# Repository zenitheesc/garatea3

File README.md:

<h1 align="center" style="color:white; background-color:black">Garatéa 3</h1>
<h4 align="center">Our aerospace probes are attached to balloons filled with helium, carrying astrobiological experiments to the stratosphere, which is crucial so we can have a better understanding about how organisms can survive in space.</h4>

<p align="center">

</p>

<p align="center">
    <a href="#what-are-aerospace-probes">What are aerospace probes?</a> •
    <a href="#project">Project</a> •
    <a href="#details">Details</a> 
</p>

## What are aerospace probes?

 Our aerospace probes are balloons filled with helium, carrying astrobiological experiments to the stratosphere, which is crucial so we can have a better understanding about how organisms can survive in space.

Although they are part of a greater scientific experiment, the probes themselves are also fascinating from the point of view of embedded systems development. Our probes are equiped with microcontrolers, radios, sensors and cameras; every mission we aim to improve our systems so we can make the next mission even more efficient.

And, to sustain all our experiments and systems, we build reliable and reusable structures, that let us go to space multiple times. 

## Project

Garatéa 3 is our most awarded Space Probe, winning 3rd Place in Best Design in the **Global Space Balloon Challenge 2018**.	This Space Probe was also a highlight at **Campus Party**. 

We continue to use the Arduino Toolchain to develop software, but we grandly improve the hardware. Our mainboard was made with 2 Atmega microcontrollers (Master/Slave) communicating through I2C. The Master was connected to the most relevant acquisition sensors, such as GPS, pressure sensor, DHT, and barometer. The data read by the Master is sent to the Slave and the Slave receive sent them through LoRa and saved them in physical memory (EEPROM and SD card). The Slave also controlled the servomotor.

Our structure is based on a **hypercube**. The external connectors were built with white ABS filament and the supports were made with a PLA filament. The center cube is made with carbon fiber plates and the external cube with carbon fiber tubes connected by the 3D printed parts.
 
### Component List

- **Main Atmega:**
    - GPS (U-Blox NEO MAX-M8Q)
    - GPS (Adafruit Ultimate Breakout)
    - Barometer (BMP180)
    - DHT sensor
    - LM1117 Regulator 
    - 7805 Regulator
- **Slave Atmega:**
    - LoRa
    - Radiometrix
    - Servomotor
    - SD card
    - EEPROM

## Details
| Launch Date |Max Altitude|Experiments|Awards
|--|--|--|--|
| 22/04/2018 | 31,6 km |Experiments with yeasts, fungi and protozoa|3rd Place in Best Design (GSBC 2018)

| | | |
|:-------------------------:|:-------------------------:|:-------------------------:|
| |  ||
|  | | | |

---

<p align="center">

</p>
<p align = "center">
<a href="zenith.eesc@gmail.com">zenith.eesc@gmail.com</a>
</p>

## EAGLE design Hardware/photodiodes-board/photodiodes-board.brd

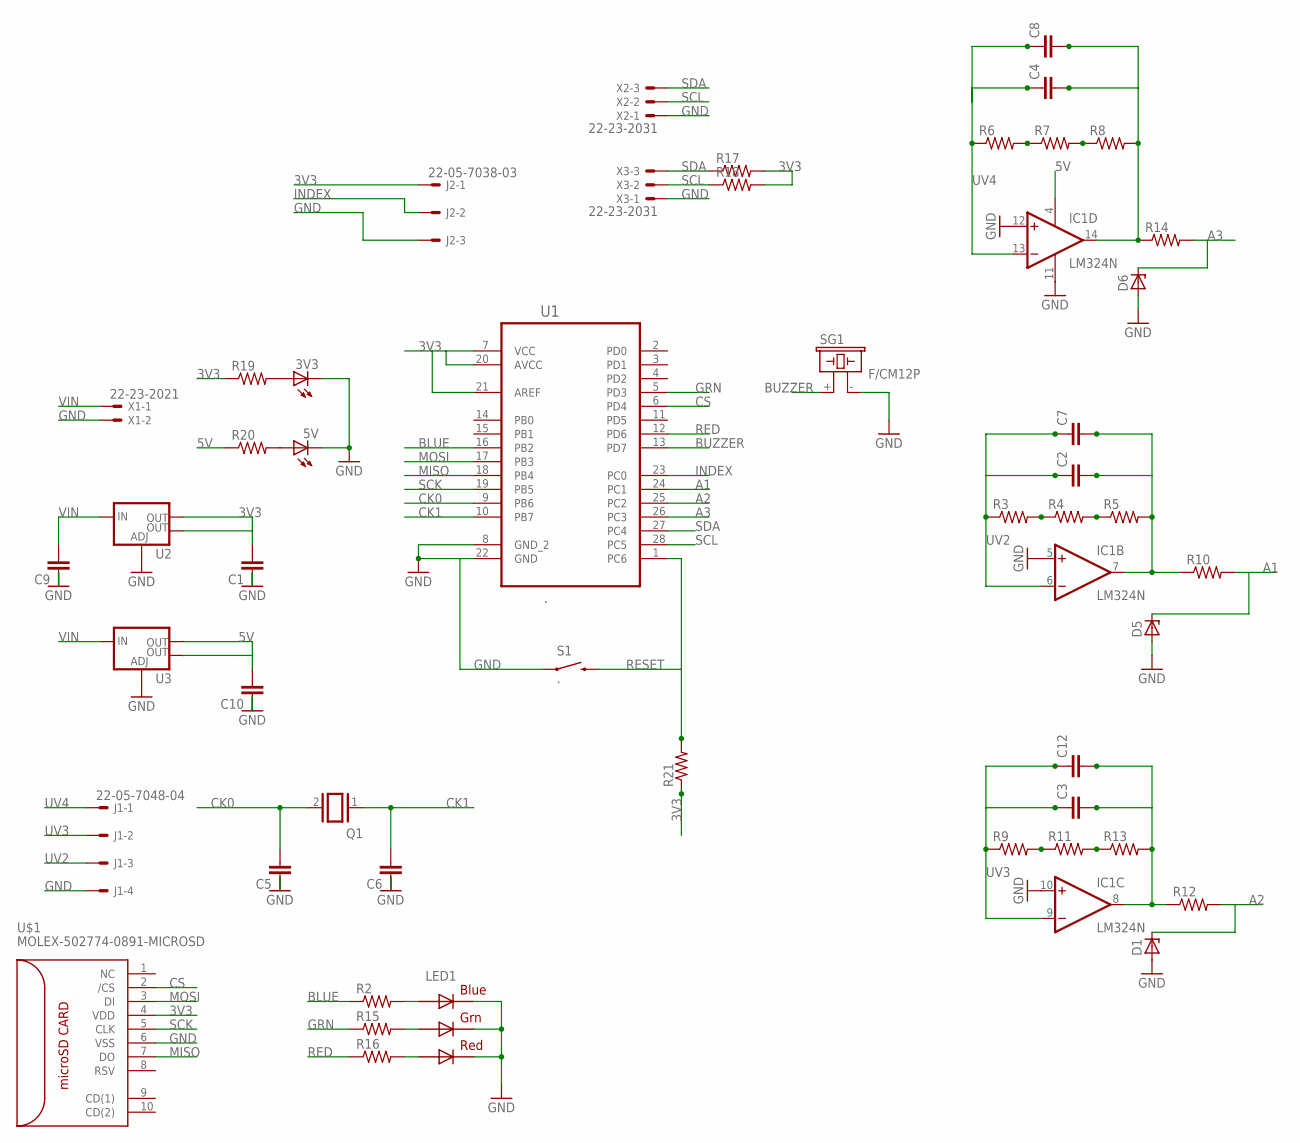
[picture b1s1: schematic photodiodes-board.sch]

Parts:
3V3, 5V: LEDSMT1206; 1206
C1, C2, C3, C4, C5, C6, C7, C8, C9, C10, C12: 10UF-1210-50V-20%; 1210
D1, D5, D6: ZENER-DIODEZD-12.5; ZDIO12.5
IC1: LM324N; DIL14
J1: 22-05-7048-04; 7395-04
J2: 22-05-7038-03; 7395-03
LED1: .; RGBLED5050
Q1: XTAL/S; QS
R2, R10, R12, R14, R15, R16, R17, R18, R19, R20, R21: R-US_M1206; M1206
R3, R4, R5, R6, R7, R8, R9, R11, R13: R-US_0207/12; 0207/12
S1: .; TACTILE-SWITCH-1101NE
SG1: F/CM12P
U1: .; DIP254P762X457-28
U2, U3: V_REG_LM1117SOT223; SOT223
U$1: MOLEX-502774-0891-MICROSD
X1: 22-23-2021
X2, X3: 22-23-2031

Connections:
3V3: C1.2, J2.1, R17.2, R18.2, R19.1, R21.1, U1.7 (VCC), U1.20 (AVCC), U1.21 (AREF), U2.2 (OUT), U2.4 (OUT), U$1.4 (VDD)
5V: C10.2, IC1.4 (V+), R20.1, U3.2 (OUT), U3.4 (OUT)
A1: D5.C, R10.2, U1.24 (PC1)
A2: D1.C, R12.2, U1.25 (PC2)
A3: D6.C, R14.2, U1.26 (PC3)
BLUE: R2.1, U1.16 (PB2)
BUZZER: SG1.+ (1), U1.13 (PD7)
CK0: C5.2, Q1.2, U1.9 (PB6)
CK1: C6.2, Q1.1, U1.10 (PB7)
CS: U1.6 (PD4), U$1.2 (/CS)
GND: 3V3.C, 5V.C, C1.1, C5.1, C6.1, C9.1, C10.1, D1.A, D5.A, D6.A, IC1.5 (+IN), IC1.10 (+IN), IC1.11 (V-), IC1.12 (+IN), J1.4, J2.3, LED1.4 (BLUE_C), LED1.5 (RED_C), LED1.6 (GREEN_C), S1.1, SG1.- (2), U1.8 (GND_2), U1.22 (GND), U2.1 (ADJ), U3.1 (ADJ), U$1.6 (VSS), X1.2, X2.1, X3.1
GRN: R15.1, U1.5 (PD3)
INDEX: J2.2, U1.23 (PC0)
MISO: U1.18 (PB4), U$1.7 (DO)
MOSI: U1.17 (PB3), U$1.3 (DI)
unnamed: R3.2, R4.1
unnamed: R4.2, R5.1
unnamed: R6.2, R7.1
unnamed: R7.2, R8.1
unnamed: R9.2, R11.1
unnamed: R11.2, R13.1
unnamed: LED1.3 (BLUE_A), R2.2
unnamed: LED1.1 (GREEN_A), R15.2
unnamed: LED1.2 (RED_A), R16.2
unnamed: 3V3.A, R19.2
unnamed: 5V.A, R20.2
unnamed: C4.2, C8.2, IC1.14 (OUT), R8.2, R14.1
unnamed: C3.2, C12.2, IC1.8 (OUT), R12.1, R13.2
unnamed: C2.2, C7.2, IC1.7 (OUT), R5.2, R10.1
RED: R16.1, U1.12 (PD6)
RESET: R21.2, S1.2, U1.1 (PC6)
SCK: U1.19 (PB5), U$1.5 (CLK)
SCL: R18.1, U1.28 (PC5), X2.2, X3.2
SDA: R17.1, U1.27 (PC4), X2.3, X3.3
UV2: C2.1, C7.1, IC1.6 (-IN), J1.3, R3.1
UV3: C3.1, C12.1, IC1.9 (-IN), J1.2, R9.1
UV4: C4.1, C8.1, IC1.13 (-IN), J1.1, R6.1
VIN: C9.2, U2.3 (IN), U3.3 (IN), X1.1

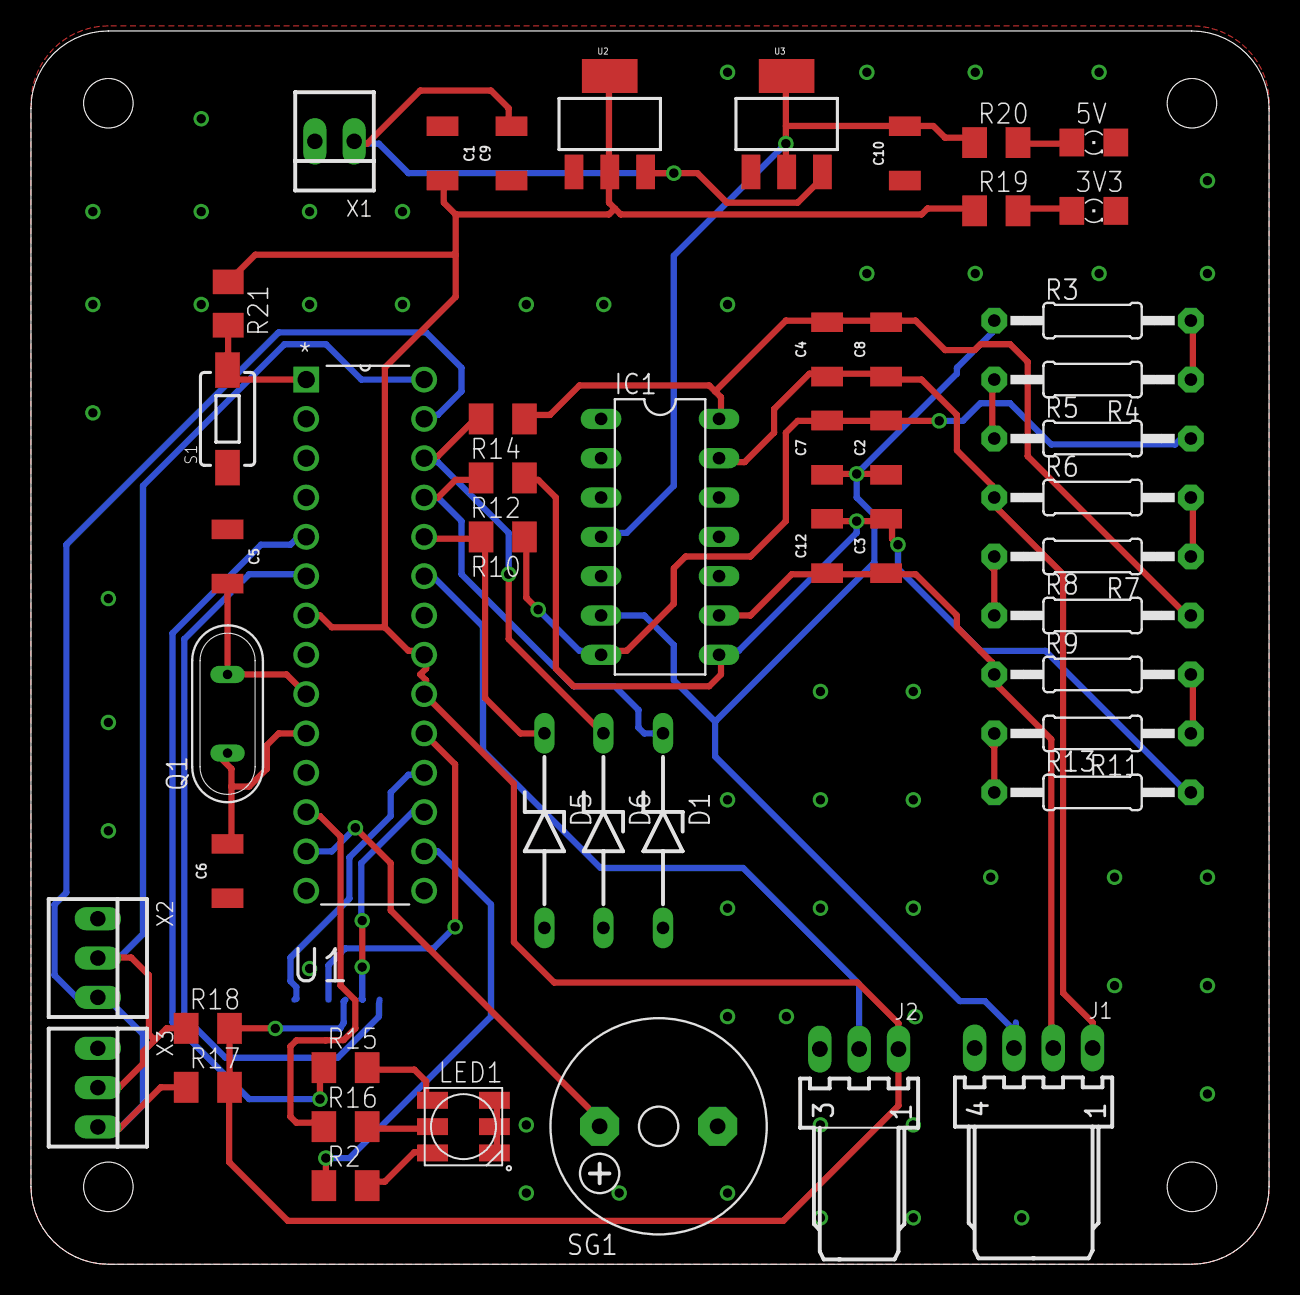
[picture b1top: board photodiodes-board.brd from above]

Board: 2 copper layers, 80.0 x 79.7 mm, 50 parts (1 on the bottom side), 38 nets.

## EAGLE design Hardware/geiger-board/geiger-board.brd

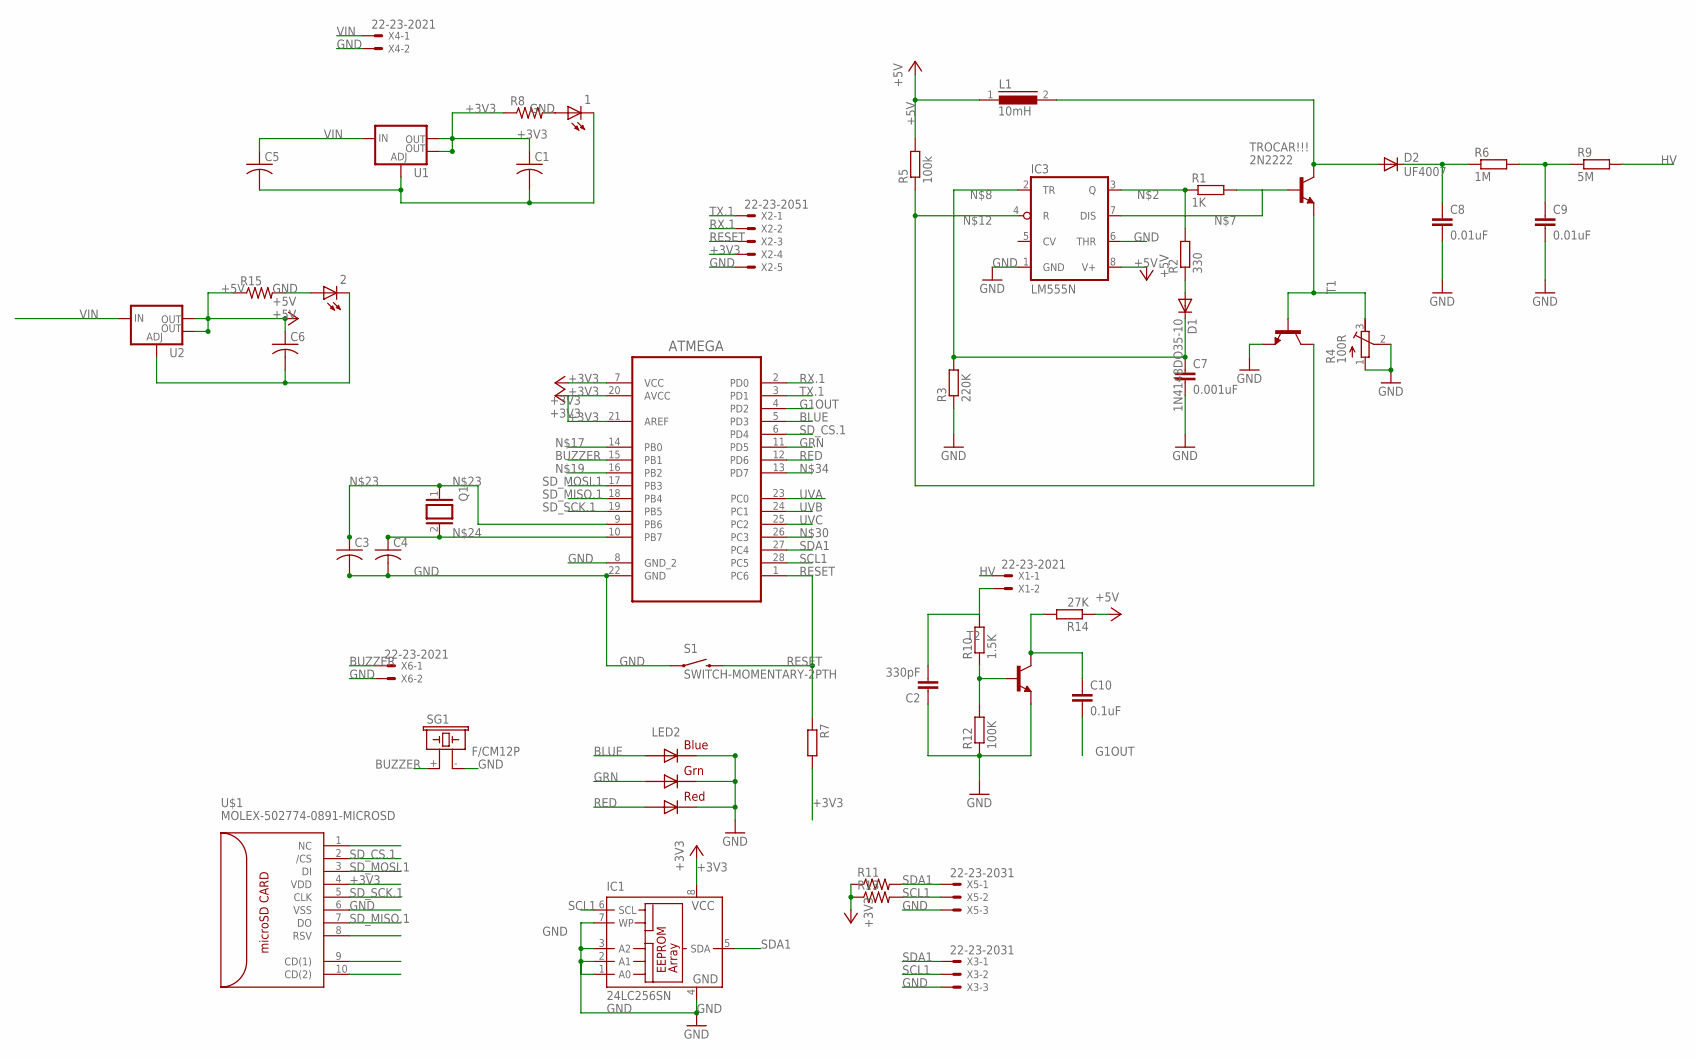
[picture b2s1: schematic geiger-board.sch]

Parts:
1, 2: LEDSMT1206; 1206
ATMEGA: ATMEGA328P-PU; DIP254P762X457-28
C1, C3, C4, C5, C6: C-USC1210K; C1210K
C2: 330pF; C5B4.5
C7: 0.001uF; C5B4.5
C8, C9: 0.01uF; C5B4.5
C10: 0.1uF; C5B4.5
D1: 1N4148DO35-10; DO35-10
D2: UF4007; DO35-10
IC1: 24LC256SN; SO-08
IC3: LM555N; DIL08-ROUND
L1: 10mH; 82114R
LED2: RGBLED5050
Q1: XTAL/S; QS
R1: 1K; 0207/10
R2: 330; 0207/10
R3: 220K; 0207/10
R4: 100R; RTRIM3296W
R5: 100k; 0207/10
R6: 1M; 0207/10
R7: R-EU_0207/10; 0207/10
R8, R15: R-US_M1206; M1206
R9: 5M; 0207/10
R10: 1.5K; 0207/10
R11, R13: R-US_R1206; R1206
R12: 100K; 0207/10
R14: 27K; 0207/10
S1: SWITCH-MOMENTARY-2PTH; TACTILE-PTH
SG1: F/CM12P
T1, T2: 2N4401-NPN-TO92-EBC; TO92-EBC
TROCAR!!!: 2N2222; TO92-EBC-OVAL
U1, U2: V_REG_LM1117SOT223; SOT223
U$1: MOLEX-502774-0891-MICROSD
X1, X4, X6: 22-23-2021
X2: 22-23-2051
X3, X5: 22-23-2031

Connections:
+3V3: ATMEGA.7 (VCC), ATMEGA.20 (AVCC), ATMEGA.21 (AREF), C1.1, IC1.8 (VCC), R7.2, R8.1, R11.1, R13.1, U1.2 (OUT), U1.4 (OUT), U$1.4 (VDD), X2.4
+5V: C6.1, IC3.8 (V+), L1.1, R5.2, R14.1, R15.1, U2.2 (OUT), U2.4 (OUT)
BLUE: ATMEGA.5 (PD3), LED2.3 (BLUE_A)
BUZZER: ATMEGA.15 (PB1), SG1.+ (1), X6.1
G1OUT: ATMEGA.4 (PD2), C10.2
GND: 1.C, 2.C, ATMEGA.8 (GND_2), ATMEGA.22 (GND), C1.2, C2.1, C3.2, C4.2, C5.2, C6.2, C7.2, C8.2, C9.2, IC1.1 (A0), IC1.2 (A1), IC1.3 (A2), IC1.4 (GND), IC1.7 (WP), IC3.1 (GND), IC3.6 (THR), LED2.4 (BLUE_C), LED2.5 (RED_C), LED2.6 (GREEN_C), R3.1, R4.1 (A), R4.2 (S), R12.1, S1.1, SG1.- (2), T1.E, T2.E, U1.1 (ADJ), U2.1 (ADJ), U$1.6 (VSS), X2.5, X3.3, X4.2, X5.3, X6.2
GRN: ATMEGA.11 (PD5), LED2.1 (GREEN_A)
HV: R9.2, X1.1
unnamed: 1.A, R8.2
unnamed: IC3.3 (Q), R1.1, R2.2
unnamed: 2.A, R15.2
unnamed: D1.A, R2.1
unnamed: IC3.7 (DIS), R1.2, TROCAR!!!.B
unnamed: C7.1, D1.C, IC3.2 (TR), R3.2
unnamed: D2.A, L1.2, TROCAR!!!.C
unnamed: C8.1, D2.C, R6.1
unnamed: IC3.4 (R), R5.1, T1.C
unnamed: C9.1, R6.2, R9.1
unnamed: C2.2, R10.2, X1.2
unnamed: R4.3 (E), T1.B, TROCAR!!!.E
unnamed: R10.1, R12.2, T2.B
unnamed: ATMEGA.9 (PB6), C3.1, Q1.1
unnamed: ATMEGA.10 (PB7), C4.1, Q1.2
unnamed: C10.1, R14.2, T2.C
RED: ATMEGA.12 (PD6), LED2.2 (RED_A)
RESET: ATMEGA.1 (PC6), R7.1, S1.3 (2), X2.3
RX.1: ATMEGA.2 (PD0), X2.2
SCL1: ATMEGA.28 (PC5), IC1.6 (SCL), R13.2, X3.2, X5.2
SDA1: ATMEGA.27 (PC4), IC1.5 (SDA), R11.2, X3.1, X5.1
SD_CS.1: ATMEGA.6 (PD4), U$1.2 (/CS)
SD_MISO.1: ATMEGA.18 (PB4), U$1.7 (DO)
SD_MOSI.1: ATMEGA.17 (PB3), U$1.3 (DI)
SD_SCK.1: ATMEGA.19 (PB5), U$1.5 (CLK)
TX.1: ATMEGA.3 (PD1), X2.1
UVA: ATMEGA.23 (PC0)
UVB: ATMEGA.24 (PC1)
UVC: ATMEGA.25 (PC2)
VIN: C5.1, U1.3 (IN), U2.3 (IN), X4.1

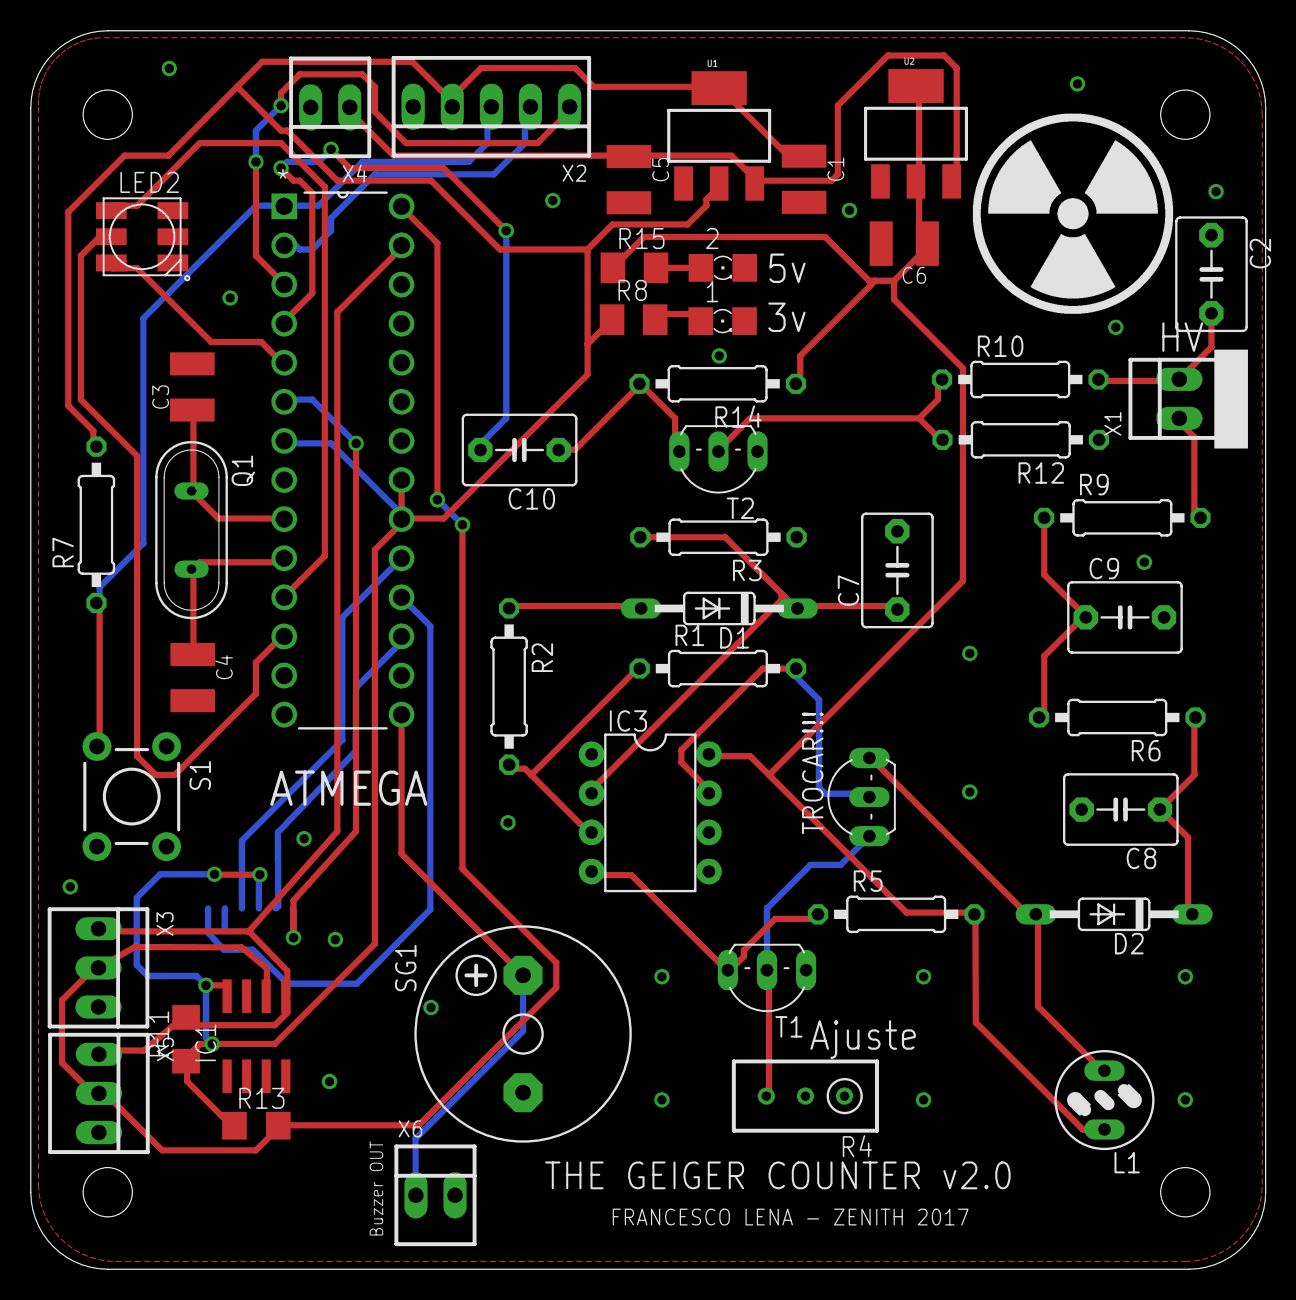
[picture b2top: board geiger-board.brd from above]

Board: 2 copper layers, 80.2 x 80.5 mm, 49 parts (1 on the bottom side), 35 nets.

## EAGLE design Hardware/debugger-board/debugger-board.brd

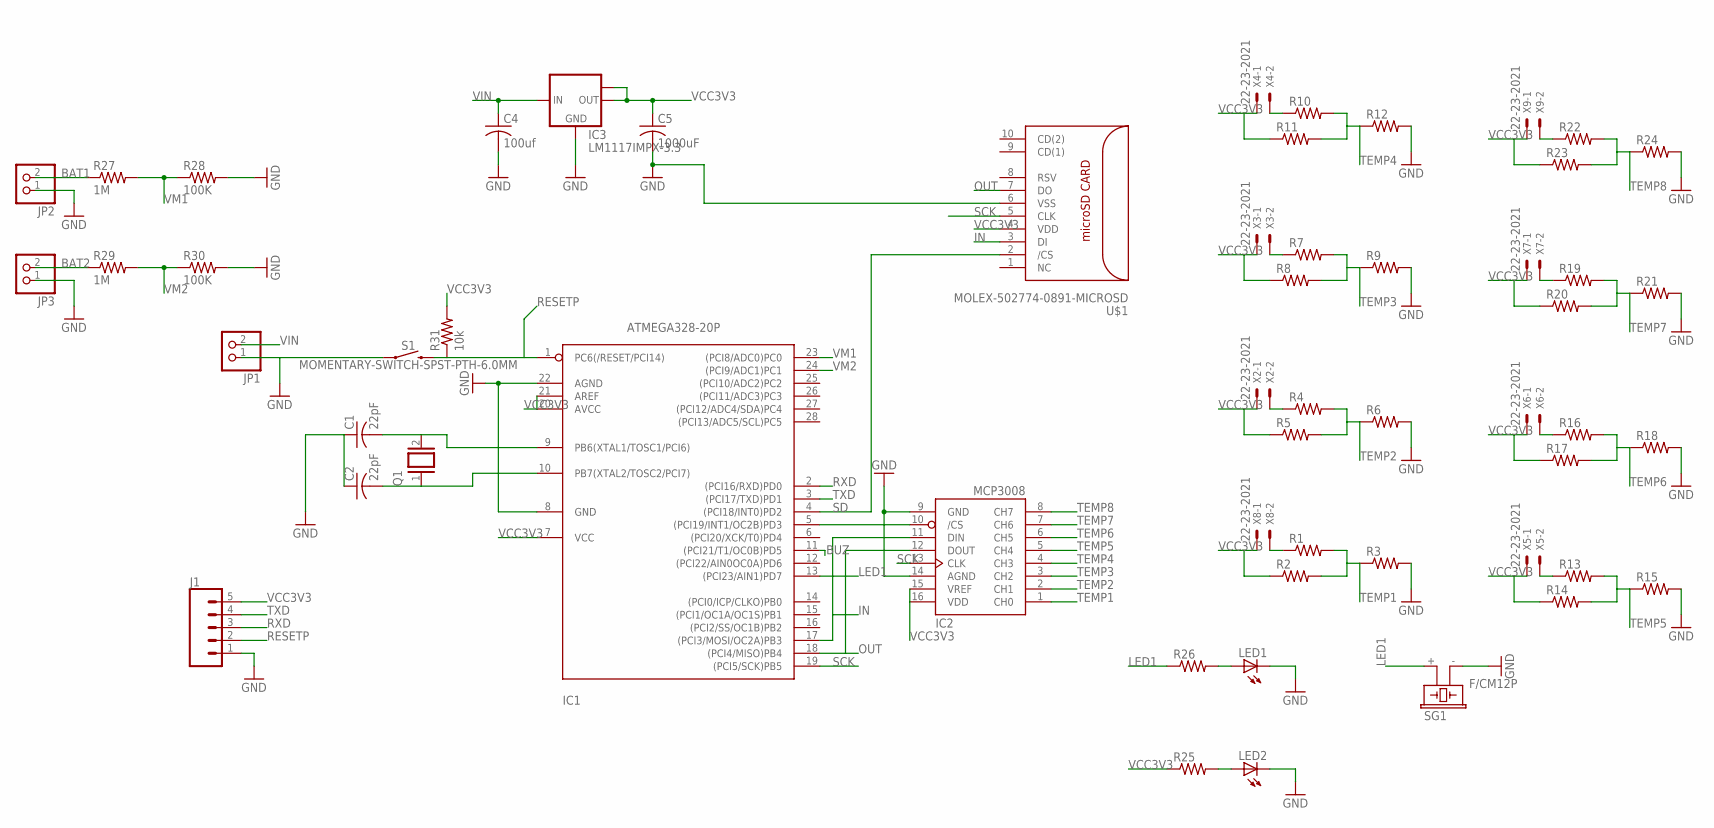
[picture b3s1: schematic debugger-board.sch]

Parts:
C1, C2: 22pF; C050-025X075
C4: 100uf; C050-025X075
C5: 1000uF; C050-025X075
IC1: ATMEGA328-20P; DIL28-3
IC2: MCP3008; DIL16
IC3: LM1117IMPX-3.3; SOT223
J1: CONN_05PTH_LONGPADS; 1X05_LONGPADS
JP1, JP2, JP3: PINHD-1X2; 1X02
LED1, LED2: LED_ELD260; LED_LD260
Q1: XTAL/S; QS
R1, R2, R3, R4, R5, R6, R7, R8, R9, R10, R11, R12, R13, R14, R15, R16, R17, R18, R19, R20, R21, R22, R23, R24, R25, R26: R-US_0204/5; 0204/5
R27, R29: 1M; 0204/5
R28, R30: 100K; 0204/5
R31: 10k; 0207/7
S1: MOMENTARY-SWITCH-SPST-PTH-6.0MM; TACTILE_SWITCH_PTH_6.0MM
SG1: F/CM12P
U$1: MOLEX-502774-0891-MICROSD
X2, X3, X4, X5, X6, X7, X8, X9: 22-23-2021

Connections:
BAT1: JP2.2, R27.1
BAT2: JP3.2, R29.1
BUZ: IC1.11 ((PCI21/T1/OC0B)PD5)
GND: C1.1, C2.1, C4.2, C5.2, IC1.8 (GND), IC1.22 (AGND), IC2.9 (GND), IC2.14 (AGND), IC3.1 (GND), J1.1, JP1.1, JP2.1, JP3.1, LED1.K (C), LED2.K (C), R3.2, R6.2, R9.2, R12.2, R15.2, R18.2, R21.2, R24.2, R28.2, R30.2, S1.1, SG1.- (2), U$1.6 (VSS)
IN: IC1.17 ((PCI3/MOSI/OC2A)PB3), IC2.11 (DIN), U$1.3 (DI)
LED1: IC1.13 ((PCI23/AIN1)PD7), R26.1, SG1.+ (1)
unnamed: LED2.A, R25.2
unnamed: IC1.5 ((PCI19/INT1/OC2B)PD3), IC2.10 (/CS)
unnamed: C1.2, IC1.9 (PB6(XTAL1/TOSC1/PCI6)), Q1.2
unnamed: C2.2, IC1.10 (PB7(XTAL2/TOSC2/PCI7)), Q1.1
unnamed: R4.1, X2.2
unnamed: R1.1, X8.2
unnamed: LED1.A, R26.2
unnamed: R7.1, X3.2
unnamed: R10.1, X4.2
unnamed: R13.1, X5.2
unnamed: R16.1, X6.2
unnamed: R19.1, X7.2
unnamed: R22.1, X9.2
OUT: IC1.18 ((PCI4/MISO)PB4), IC2.12 (DOUT), U$1.7 (DO)
RESETP: IC1.1 (PC6(/RESET/PCI14)), J1.2, R31.1, S1.3 (2)
RXD: IC1.2 ((PCI16/RXD)PD0), J1.3
SCK: IC1.19 ((PCI5/SCK)PB5), IC2.13 (CLK), U$1.5 (CLK)
SD: IC1.4 ((PCI18/INT0)PD2), U$1.2 (/CS)
TEMP1: IC2.1 (CH0), R1.2, R2.2, R3.1
TEMP2: IC2.2 (CH1), R4.2, R5.2, R6.1
TEMP3: IC2.3 (CH2), R7.2, R8.2, R9.1
TEMP4: IC2.4 (CH3), R10.2, R11.2, R12.1
TEMP5: IC2.5 (CH4), R13.2, R14.2, R15.1
TEMP6: IC2.6 (CH5), R16.2, R17.2, R18.1
TEMP7: IC2.7 (CH6), R19.2, R20.2, R21.1
TEMP8: IC2.8 (CH7), R22.2, R23.2, R24.1
TXD: IC1.3 ((PCI17/TXD)PD1), J1.4
VCC3V3: C5.1, IC1.7 (VCC), IC1.20 (AVCC), IC1.21 (AREF), IC2.15 (VREF), IC2.16 (VDD), IC3.2 (OUT), IC3.TAB (OUT1), J1.5, R2.1, R5.1, R8.1, R11.1, R14.1, R17.1, R20.1, R23.1, R25.1, R31.2, U$1.4 (VDD), X2.1, X3.1, X4.1, X5.1, X6.1, X7.1, X8.1, X9.1
VIN: C4.1, IC3.3 (IN), JP1.2
VM1: IC1.23 ((PCI8/ADC0)PC0), R27.2, R28.1
VM2: IC1.24 ((PCI9/ADC1)PC1), R29.2, R30.1

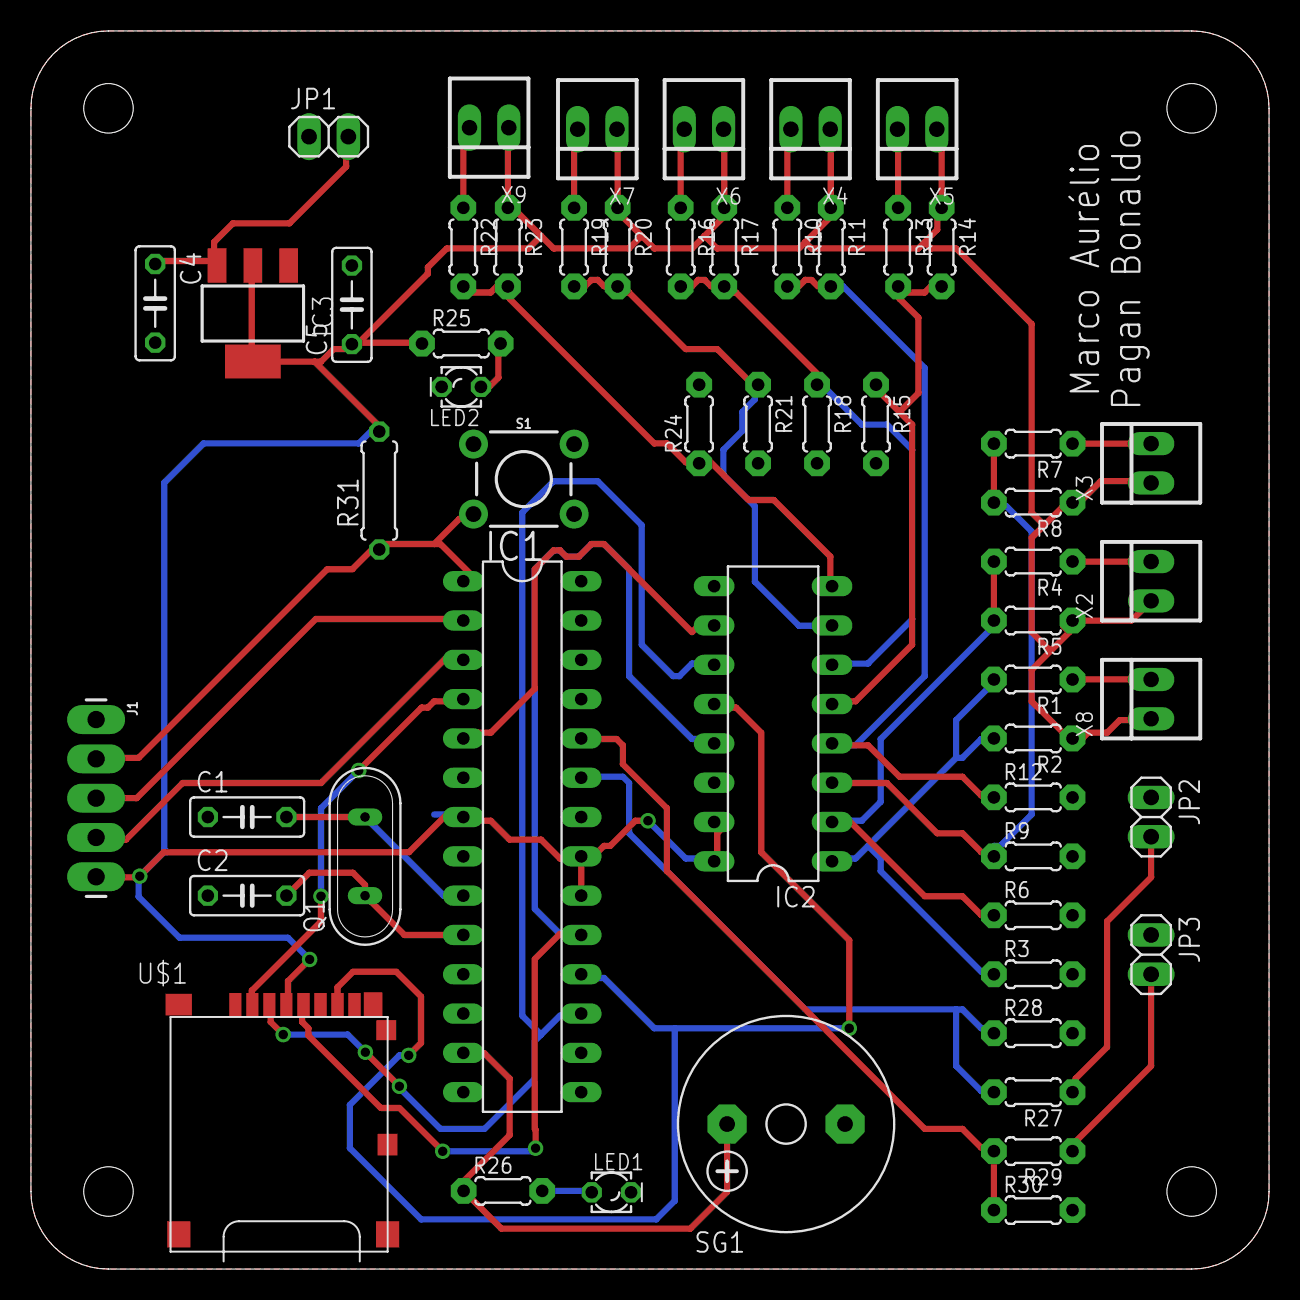
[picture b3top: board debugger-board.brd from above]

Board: 2 copper layers, 80.0 x 80.0 mm, 56 parts (0 on the bottom side), 36 nets.

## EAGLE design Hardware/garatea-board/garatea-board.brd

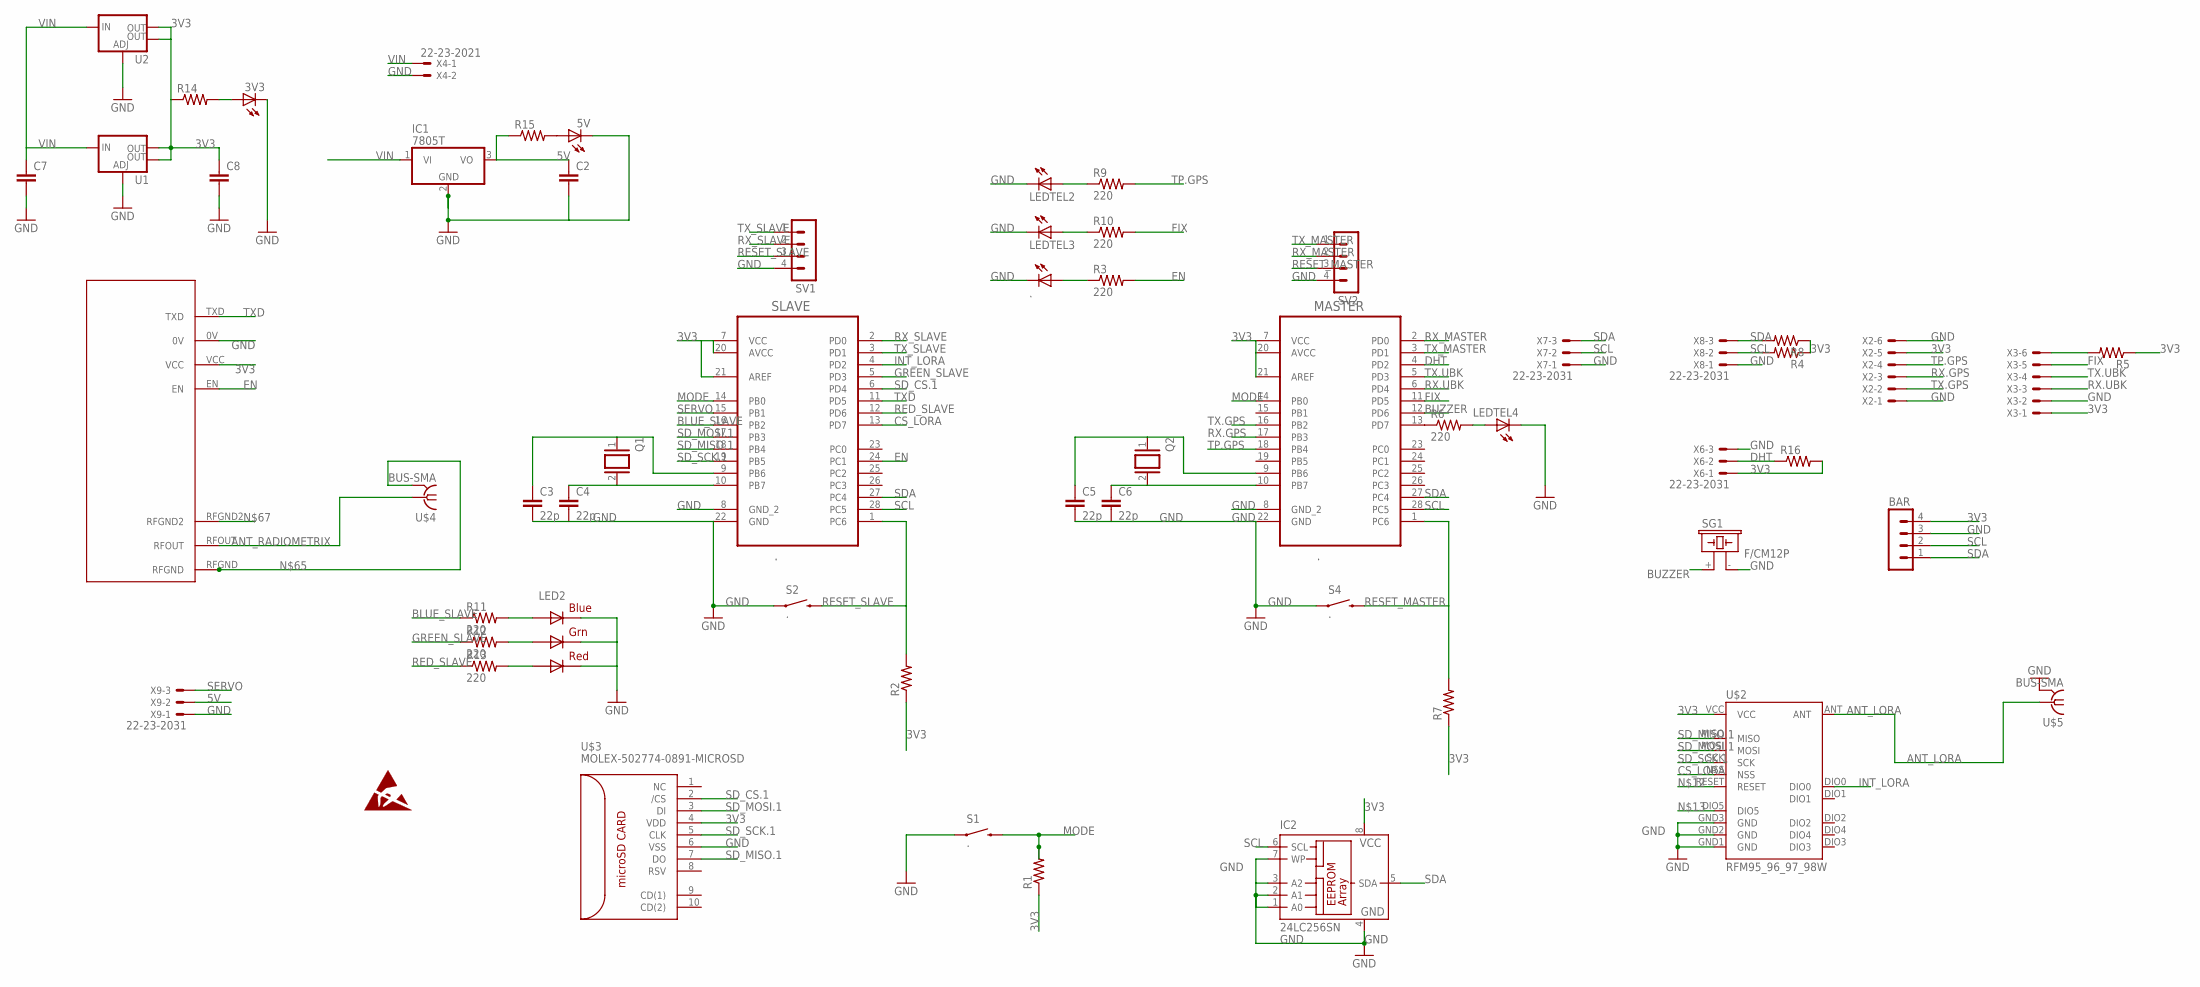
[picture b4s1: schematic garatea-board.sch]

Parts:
3V3, 5V, .: LEDSMT1206; 1206
BAR: MA04-1
C2, C7, C8: 10UF-1210-50V-20%; 1210
C3, C4, C5, C6: 22p; 1210
IC1: 7805T; TO220H
IC2: 24LC256SN; SO-08
LED2: RGBLED5050
LEDTEL2, LEDTEL3, LEDTEL4: LEDSMT1206; 1206
MASTER: .; DIP254P762X457-28
Q1, Q2: XTAL/S; QS
R1, R2, R4, R5, R7, R8, R14, R15, R16: R-US_M1206; M1206
R3, R6, R9, R10, R11, R12, R13: 220; M1206
S1, S2, S4: .; TACTILE-SWITCH-1101NE
SG1: F/CM12P
SLAVE: .; DIP254P762X457-28
SV1, SV2: MA04-1
U1, U2: V_REG_LM1117SOT223; SOT223
U$1: NTX2
U$2: RFM95_96_97_98W
U$3: MOLEX-502774-0891-MICROSD
U$4, U$5: BUS-SMA
X2, X3: 22-23-2061
X4: 22-23-2021
X6, X7, X8, X9: 22-23-2031

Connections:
3V3: BAR.4, C8.1, IC2.8 (VCC), MASTER.7 (VCC), MASTER.20 (AVCC), MASTER.21 (AREF), R1.1, R2.1, R4.1, R5.1, R7.1, R8.1, R14.1, R16.2, SLAVE.7 (VCC), SLAVE.20 (AVCC), SLAVE.21 (AREF), U1.2 (OUT), U1.4 (OUT), U2.2 (OUT), U2.4 (OUT), U$1.VCC, U$2.VCC, U$3.4 (VDD), X2.5, X3.1, X6.1
5V: C2.1, IC1.3 (VO), R15.1, X9.2
ANT_LORA: U$2.ANT, U$5.1
ANT_RADIOMETRIX: U$1.RFOUT, U$4.1
BLUE_SLAVE: R11.1, SLAVE.16 (PB2)
BUZZER: MASTER.12 (PD6), SG1.+ (1)
CS_LORA: SLAVE.13 (PD7), U$2.NSS
DHT: MASTER.4 (PD2), R16.1, X6.2
EN: R3.2, SLAVE.24 (PC1), U$1.EN
EN.UBK: R5.2, X3.6
FIX: MASTER.11 (PD5), R10.2, X3.5
GND: 3V3.C, 5V.C, ..C, BAR.3, C2.2, C3.2, C4.2, C5.2, C6.2, C7.2, C8.2, IC1.2 (GND), IC2.1 (A0), IC2.2 (A1), IC2.3 (A2), IC2.4 (GND), IC2.7 (WP), LED2.4 (BLUE_C), LED2.5 (RED_C), LED2.6 (GREEN_C), LEDTEL2.C, LEDTEL3.C, LEDTEL4.C, MASTER.8 (GND_2), MASTER.22 (GND), S1.1, S2.1, S4.1, SG1.- (2), SLAVE.8 (GND_2), SLAVE.22 (GND), SV1.4, SV2.4, U1.1 (ADJ), U2.1 (ADJ), U$1.0V, U$2.GND1 (GND), U$2.GND2 (GND), U$2.GND3 (GND), U$3.6 (VSS), U$5.2 (GND), U$5.3 (GND), U$5.4 (GND), U$5.5 (GND), X2.1, X2.6, X3.2, X4.2, X6.3, X7.1, X8.1, X9.1
GREEN_SLAVE: R12.1, SLAVE.5 (PD3)
INT_LORA: SLAVE.4 (PD2), U$2.DIO0
MODE: MASTER.14 (PB0), R1.2, S1.2, SLAVE.14 (PB0)
unnamed: MASTER.13 (PD7), R6.1
unnamed: LEDTEL3.A, R10.1
unnamed: LEDTEL2.A, R9.1
unnamed: ..A, R3.1
unnamed: 5V.A, R15.2
unnamed: LED2.3 (BLUE_A), R11.2
unnamed: LED2.1 (GREEN_A), R12.2
unnamed: LED2.2 (RED_A), R13.2
unnamed: 3V3.A, R14.2
unnamed: C6.1, MASTER.10 (PB7), Q2.2
unnamed: LEDTEL4.A, R6.2
unnamed: C3.1, Q1.1, SLAVE.9 (PB6)
unnamed: C4.1, Q1.2, SLAVE.10 (PB7)
unnamed: C5.1, MASTER.9 (PB6), Q2.1
unnamed: U$1.RFGND, U$4.2 (GND), U$4.3 (GND), U$4.4 (GND), U$4.5 (GND)
RED_SLAVE: R13.1, SLAVE.12 (PD6)
RESET_MASTER: MASTER.1 (PC6), R7.2, S4.2, SV2.3
RESET_SLAVE: R2.2, S2.2, SLAVE.1 (PC6), SV1.3
RX.GPS: MASTER.17 (PB3), X2.3
RX.UBK: MASTER.6 (PD4), X3.3
RX_MASTER: MASTER.2 (PD0), SV2.2
RX_SLAVE: SLAVE.2 (PD0), SV1.2
SCL: BAR.2, IC2.6 (SCL), MASTER.28 (PC5), R4.2, SLAVE.28 (PC5), X7.2, X8.2
SDA: BAR.1, IC2.5 (SDA), MASTER.27 (PC4), R8.2, SLAVE.27 (PC4), X7.3, X8.3
SD_CS.1: SLAVE.6 (PD4), U$3.2 (/CS)
SD_MISO.1: SLAVE.18 (PB4), U$2.MISO, U$3.7 (DO)
SD_MOSI.1: SLAVE.17 (PB3), U$2.MOSI, U$3.3 (DI)
SD_SCK.1: SLAVE.19 (PB5), U$2.SCK, U$3.5 (CLK)
SERVO: SLAVE.15 (PB1), X9.3
TP.GPS: MASTER.18 (PB4), R9.2, X2.4
TX.GPS: MASTER.16 (PB2), X2.2
TX.UBK: MASTER.5 (PD3), X3.4
TXD: SLAVE.11 (PD5), U$1.TXD
TX_MASTER: MASTER.3 (PD1), SV2.1
TX_SLAVE: SLAVE.3 (PD1), SV1.1
VIN: C7.1, IC1.1 (VI), U1.3 (IN), U2.3 (IN), X4.1

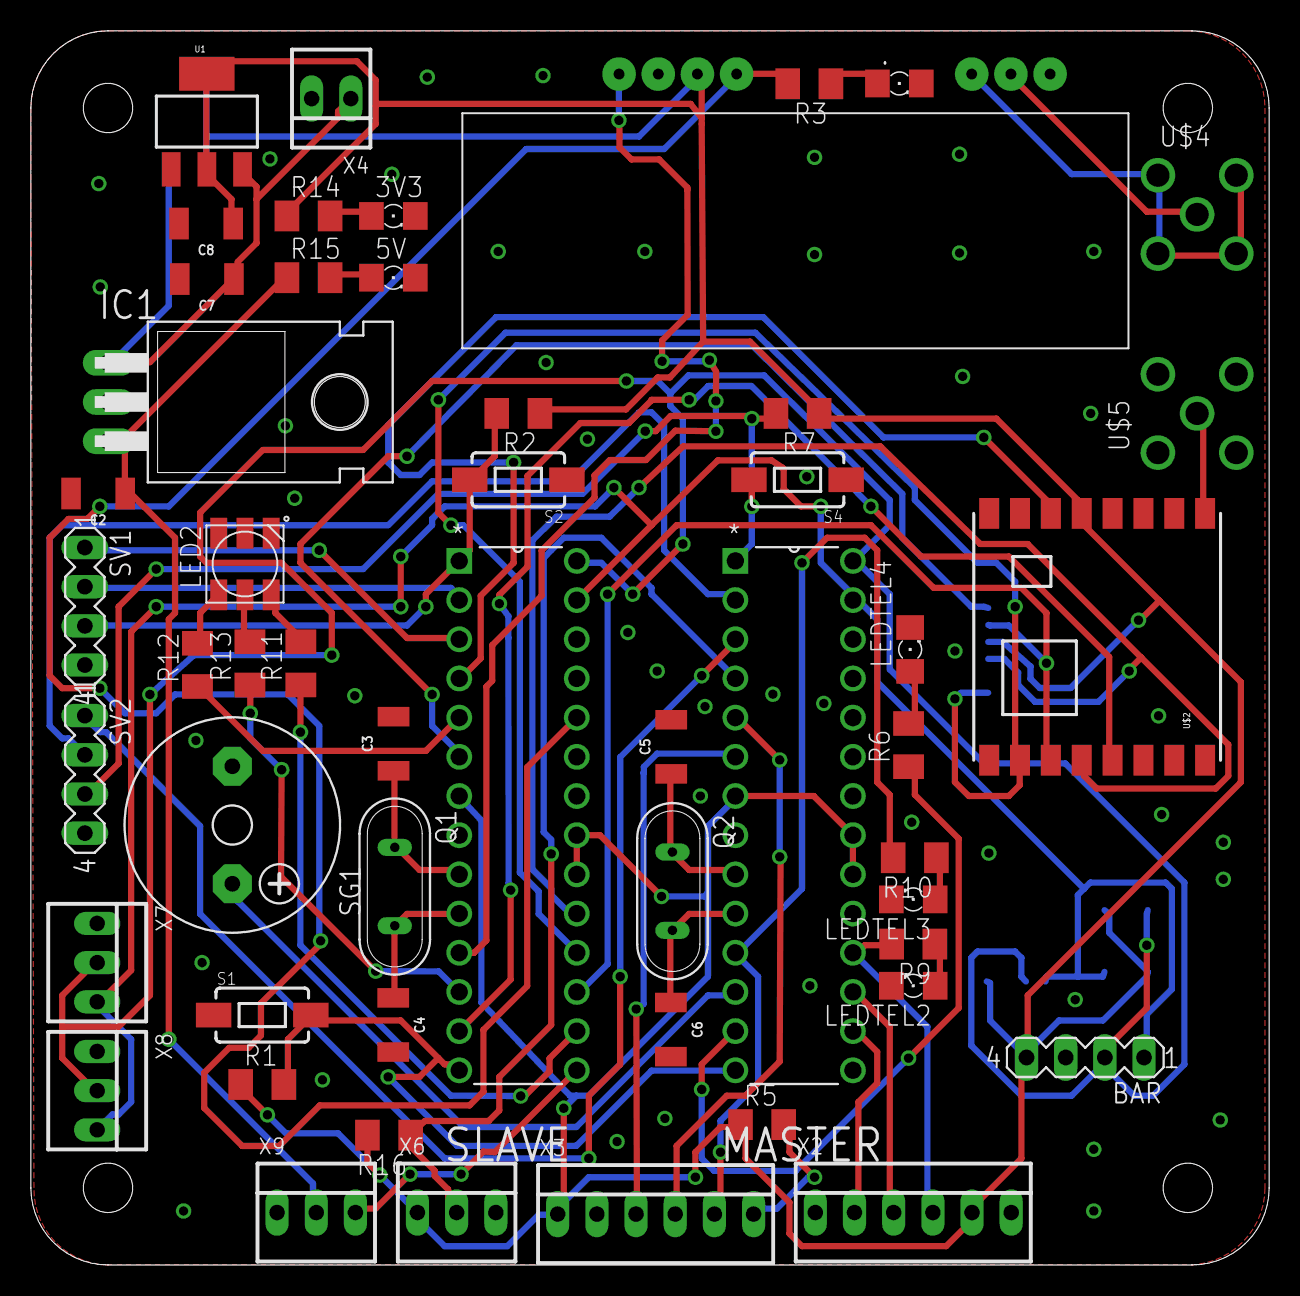
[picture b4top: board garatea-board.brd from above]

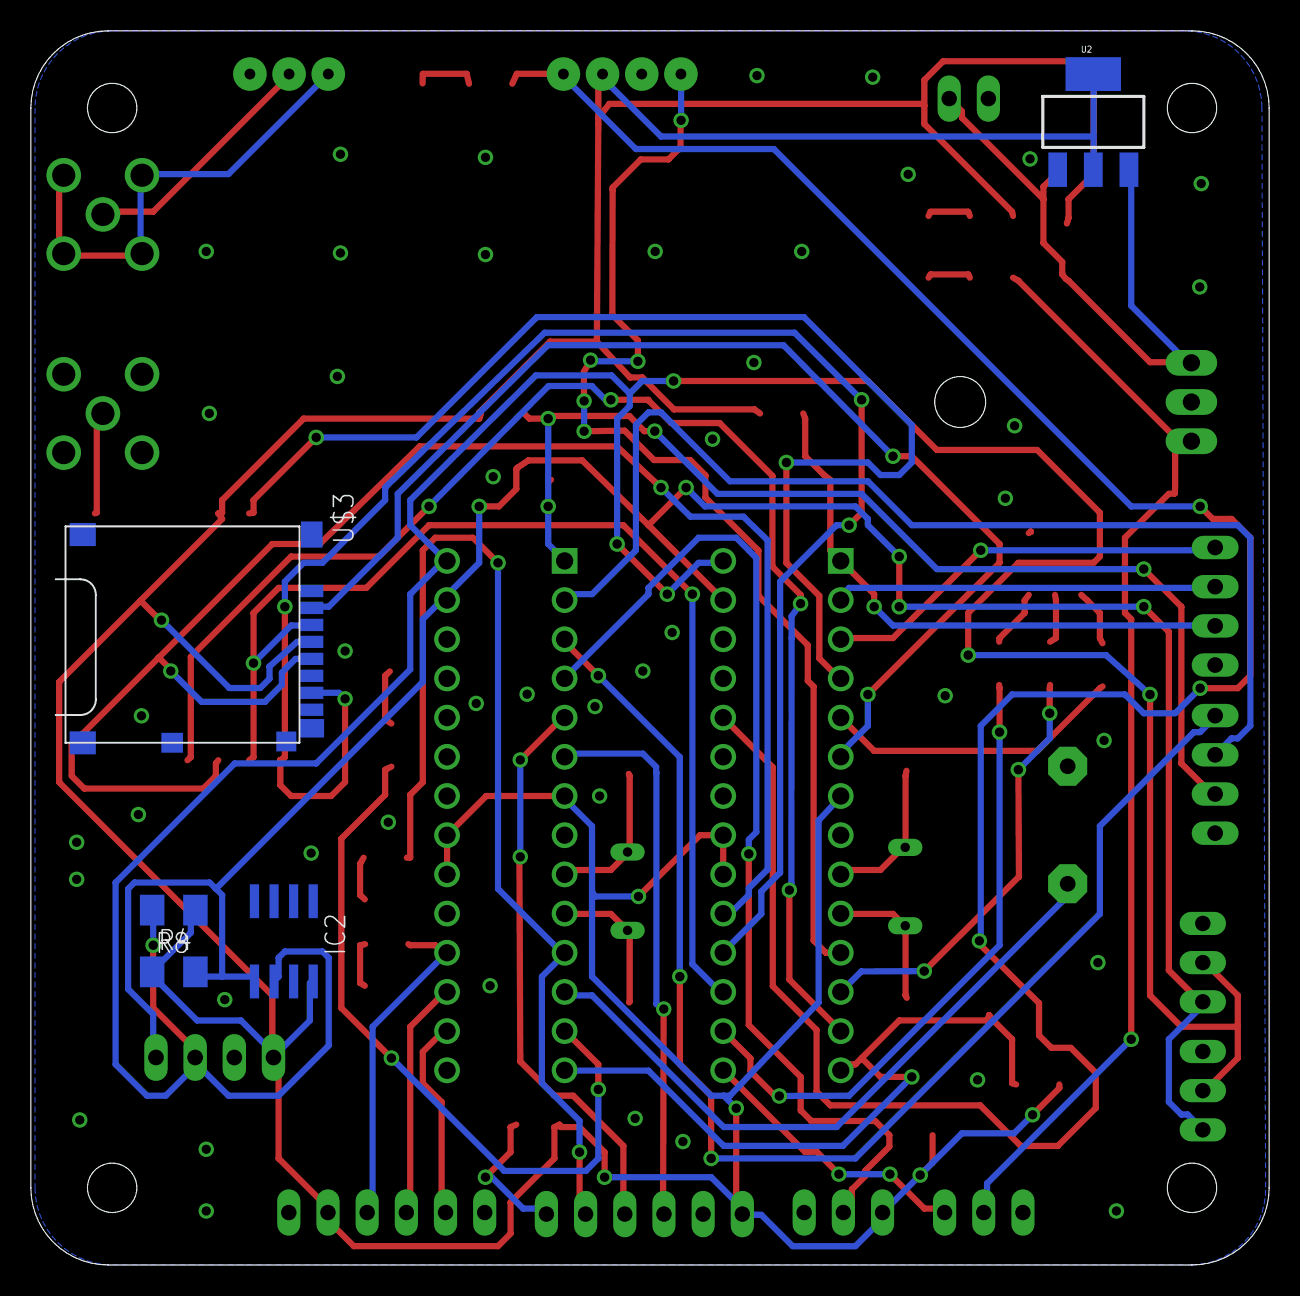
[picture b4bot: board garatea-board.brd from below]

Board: 2 copper layers, 80.3 x 80.0 mm, 57 parts (5 on the bottom side), 51 nets.

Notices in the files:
parts and their libraries:
SparkFun-Switches: Licensing: Creative Commons ShareAlike 4.0 International - https://creativecommons.org/licenses/by-sa/4.0
